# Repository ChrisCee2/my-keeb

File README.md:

# Salsa
Creating a keyboard (Inspired by Littlefoot)<br/>

Images of Type-C pcb:
<br/>

<br/>

<br/>
Guides used:
<br/>
https://wiki.ai03.com/books/pcb-design/page/pcb-guide-part-1---preparations
<br/>
https://www.masterzen.fr/2020/05/03/designing-a-keyboard-part-1/

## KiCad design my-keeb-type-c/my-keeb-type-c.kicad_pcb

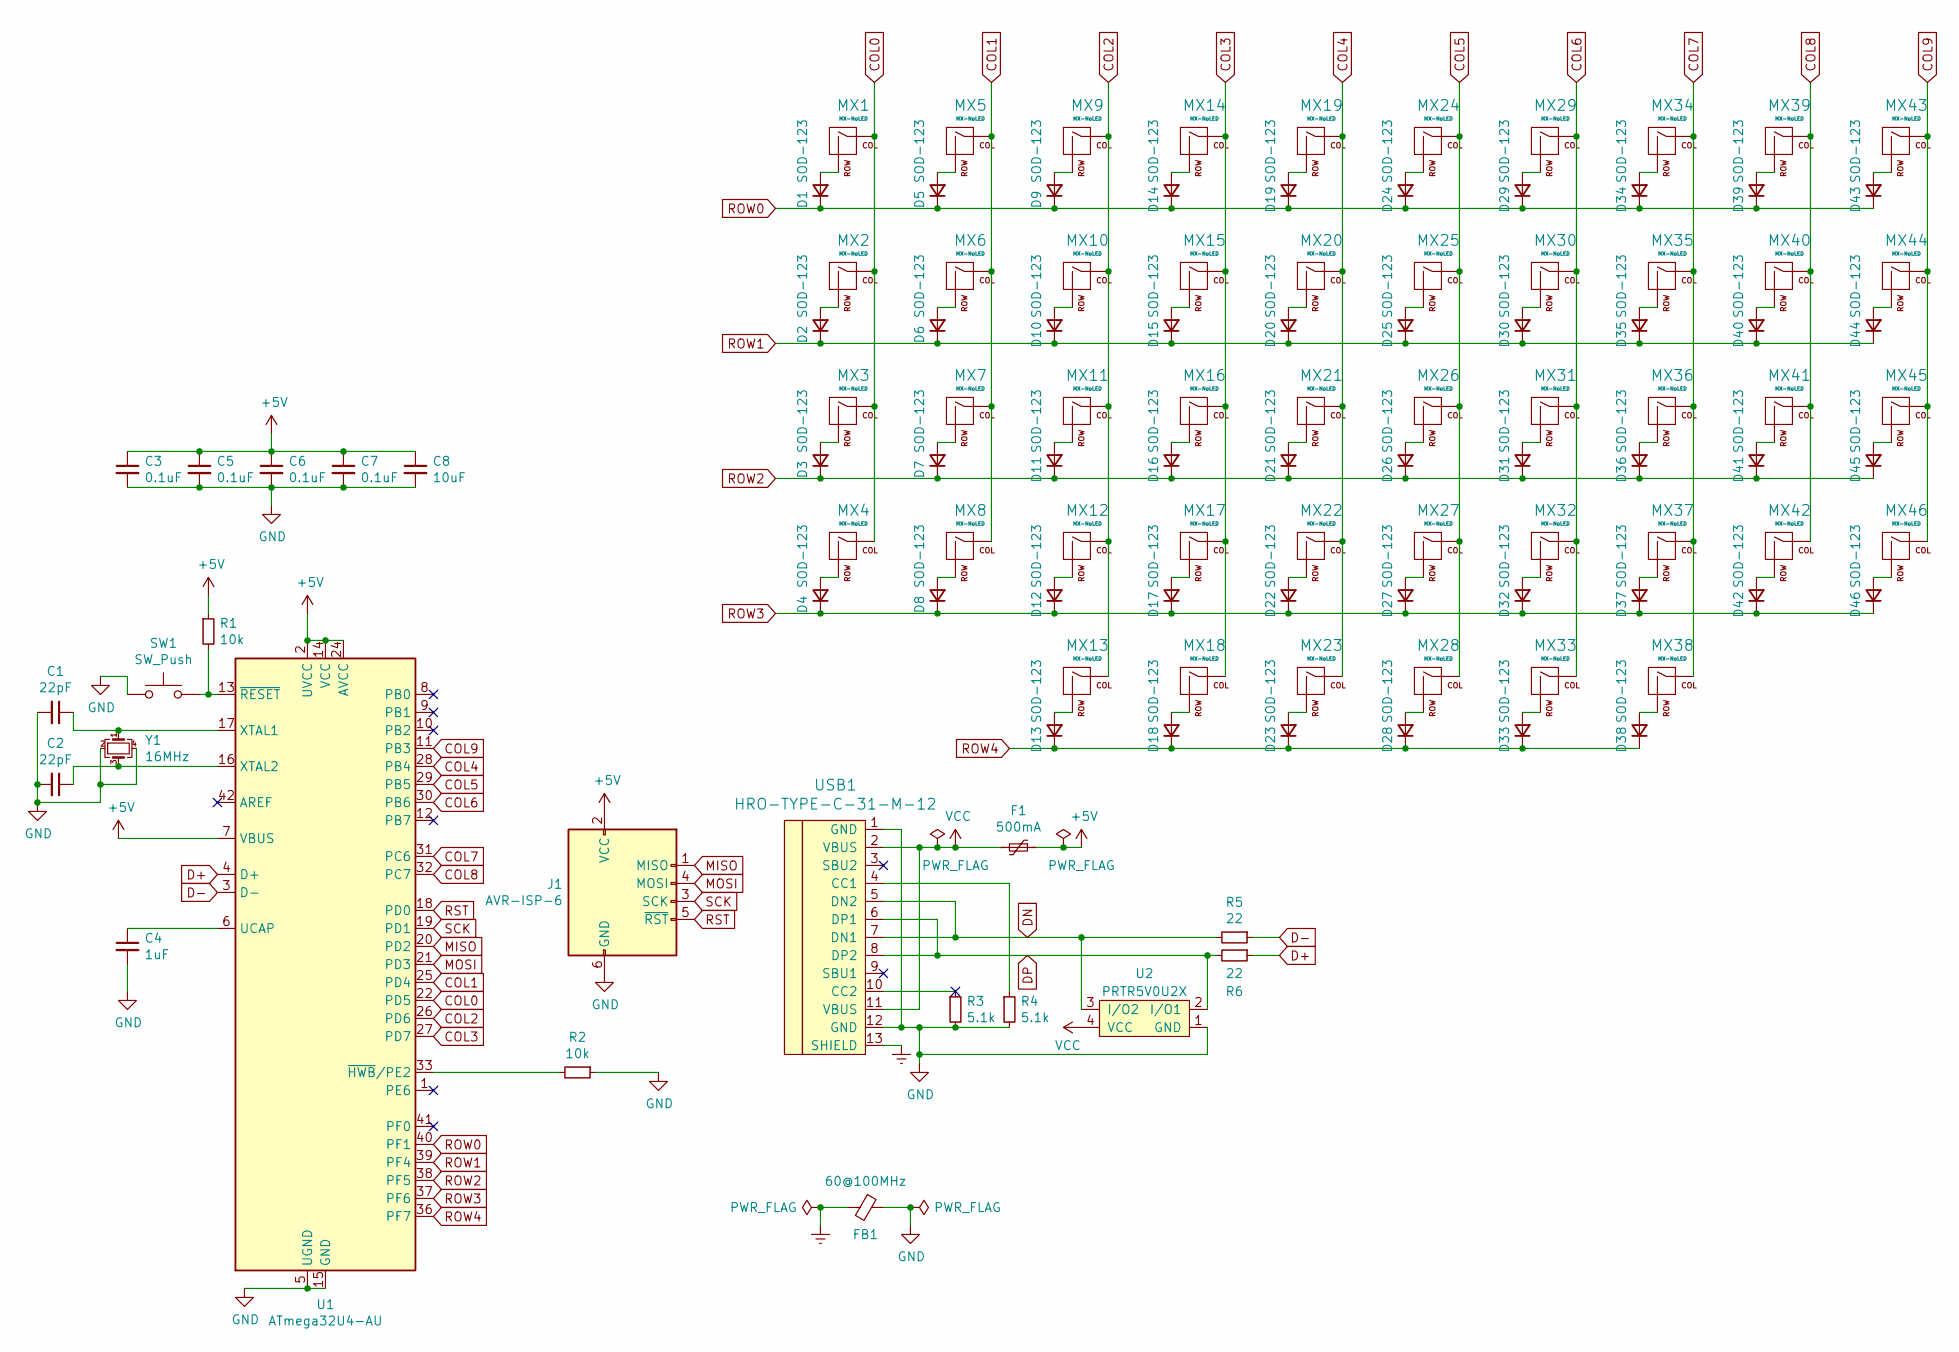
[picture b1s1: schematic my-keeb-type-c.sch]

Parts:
C1, C2: 22pF; C_0805_2012Metric_Pad1.18x1.45mm_HandSolder
C3, C5, C6, C7: 0.1uF; C_0805_2012Metric_Pad1.18x1.45mm_HandSolder
C4: 1uF; C_0805_2012Metric_Pad1.18x1.45mm_HandSolder
C8: 10uF; C_0805_2012Metric_Pad1.18x1.45mm_HandSolder
D1, D2, D3, D4, D5, D6, D7, D8, D9, D10, D11, D12, D13, D14, D15, D16, D17, D18, D19, D20, D21, D22, D23, D24, D25, D26, D27, D28, D29, D30, D31, D32, D33, D34, D35, D36, D37, D38, D39, D40, D41, D42, D43, D44, D45, D46: SOD-123; D_SOD-123
F1: 500mA; Fuse_1206_3216Metric_Pad1.42x1.75mm_HandSolder
FB1: 60@100MHz; L_0805_2012Metric_Pad1.15x1.40mm_HandSolder
J1: AVR-ISP-6; Reset_Pretty-Mask
MX1, MX2, MX3, MX4, MX5, MX6, MX7, MX8, MX9, MX10, MX11, MX12, MX13, MX14, MX15, MX16, MX17, MX18, MX19, MX20, MX21, MX22, MX24, MX25, MX26, MX27, MX29, MX30, MX31, MX32, MX33, MX34, MX35, MX36, MX37, MX38, MX39, MX40, MX41, MX42, MX43, MX44, MX45, MX46: MX-NoLED; MX-1U-NoLED
MX23, MX28: MX-NoLED; MX-1.5U-NoLED
R1, R2: 10k; R_0805_2012Metric_Pad1.20x1.40mm_HandSolder
R3, R4: 5.1k; R_0805_2012Metric_Pad1.20x1.40mm_HandSolder
R5, R6: 22; R_0805_2012Metric_Pad1.20x1.40mm_HandSolder
SW1: SW_Push; SW_SPST_SKQG_WithStem
U1: ATmega32U4-AU; TQFP-44_10x10mm_P0.8mm
U2: PRTR5V0U2X; SOT143B
USB1: HRO-TYPE-C-31-M-12; HRO-TYPE-C-31-M-12-HandSoldering
Y1: 16MHz; Crystal_SMD_3225-4Pin_3.2x2.5mm_HandSoldering

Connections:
+5V: C3.1, C5.1, C6.1, C7.1, C8.1, F1.1, J1.2 (VCC), R1.1, U1.2 (UVCC), U1.7 (VBUS), U1.14 (VCC), U1.24 (AVCC), U1.34 (VCC), U1.44 (AVCC)
COL0: MX1.1 (COL), MX2.1 (COL), MX3.1 (COL), MX4.1 (COL), U1.22 (PD5)
COL1: MX5.1 (COL), MX6.1 (COL), MX7.1 (COL), MX8.1 (COL), U1.25 (PD4)
COL2: MX9.1 (COL), MX10.1 (COL), MX11.1 (COL), MX12.1 (COL), MX13.1 (COL), U1.26 (PD6)
COL3: MX14.1 (COL), MX15.1 (COL), MX16.1 (COL), MX17.1 (COL), MX18.1 (COL), U1.27 (PD7)
COL4: MX19.1 (COL), MX20.1 (COL), MX21.1 (COL), MX22.1 (COL), MX23.1 (COL), U1.28 (PB4)
COL5: MX24.1 (COL), MX25.1 (COL), MX26.1 (COL), MX27.1 (COL), MX28.1 (COL), U1.29 (PB5)
COL6: MX29.1 (COL), MX30.1 (COL), MX31.1 (COL), MX32.1 (COL), MX33.1 (COL), U1.30 (PB6)
COL7: MX34.1 (COL), MX35.1 (COL), MX36.1 (COL), MX37.1 (COL), MX38.1 (COL), U1.31 (PC6)
COL8: MX39.1 (COL), MX40.1 (COL), MX41.1 (COL), MX42.1 (COL), U1.32 (PC7)
COL9: MX43.1 (COL), MX44.1 (COL), MX45.1 (COL), MX46.1 (COL), U1.11 (PB3)
D+: R6.1, U1.4 (D+)
D-: R5.1, U1.3 (D-)
DN: R5.2, U2.3 (I/O2), USB1.5 (DN2), USB1.7 (DN1)
DP: R6.2, U2.2 (I/O1), USB1.6 (DP1), USB1.8 (DP2)
Earth: FB1.2, USB1.13 (SHIELD)
GND: C1.2, C2.2, C3.2, C4.2, C5.2, C6.2, C7.2, C8.2, FB1.1, J1.6 (GND), R2.1, R3.2, R4.2, SW1.1, U1.5 (UGND), U1.15 (GND), U1.23 (GND), U1.35 (GND), U1.43 (GND), U2.1 (GND), USB1.1 (GND), USB1.12 (GND), Y1.2, Y1.4
MISO: J1.1 (MISO), U1.20 (PD2)
MOSI: J1.4 (MOSI), U1.21 (PD3)
unnamed: C1.1, U1.17 (XTAL1), Y1.1
unnamed: C2.1, U1.16 (XTAL2), Y1.3
unnamed: C4.1, U1.6 (UCAP)
unnamed: D1.2 (A), MX1.2 (ROW)
unnamed: D2.2 (A), MX2.2 (ROW)
unnamed: D3.2 (A), MX3.2 (ROW)
unnamed: D4.2 (A), MX4.2 (ROW)
unnamed: D5.2 (A), MX5.2 (ROW)
unnamed: D6.2 (A), MX6.2 (ROW)
unnamed: D7.2 (A), MX7.2 (ROW)
unnamed: D8.2 (A), MX8.2 (ROW)
unnamed: D9.2 (A), MX9.2 (ROW)
unnamed: D10.2 (A), MX10.2 (ROW)
unnamed: D11.2 (A), MX11.2 (ROW)
unnamed: D12.2 (A), MX12.2 (ROW)
unnamed: D13.2 (A), MX13.2 (ROW)
unnamed: D14.2 (A), MX14.2 (ROW)
unnamed: D15.2 (A), MX15.2 (ROW)
unnamed: D16.2 (A), MX16.2 (ROW)
unnamed: D17.2 (A), MX17.2 (ROW)
unnamed: D18.2 (A), MX18.2 (ROW)
unnamed: D19.2 (A), MX19.2 (ROW)
unnamed: D20.2 (A), MX20.2 (ROW)
unnamed: D21.2 (A), MX21.2 (ROW)
unnamed: D22.2 (A), MX22.2 (ROW)
unnamed: D23.2 (A), MX23.2 (ROW)
unnamed: D24.2 (A), MX24.2 (ROW)
unnamed: D25.2 (A), MX25.2 (ROW)
unnamed: D26.2 (A), MX26.2 (ROW)
unnamed: D27.2 (A), MX27.2 (ROW)
unnamed: D28.2 (A), MX28.2 (ROW)
unnamed: D29.2 (A), MX29.2 (ROW)
unnamed: D30.2 (A), MX30.2 (ROW)
unnamed: D31.2 (A), MX31.2 (ROW)
unnamed: D32.2 (A), MX32.2 (ROW)
unnamed: D33.2 (A), MX33.2 (ROW)
unnamed: D34.2 (A), MX34.2 (ROW)
unnamed: D35.2 (A), MX35.2 (ROW)
unnamed: D36.2 (A), MX36.2 (ROW)
unnamed: D37.2 (A), MX37.2 (ROW)
unnamed: D38.2 (A), MX38.2 (ROW)
unnamed: D39.2 (A), MX39.2 (ROW)
unnamed: D40.2 (A), MX40.2 (ROW)
unnamed: D41.2 (A), MX41.2 (ROW)
unnamed: D42.2 (A), MX42.2 (ROW)
unnamed: D43.2 (A), MX43.2 (ROW)
unnamed: D44.2 (A), MX44.2 (ROW)
unnamed: D45.2 (A), MX45.2 (ROW)
unnamed: D46.2 (A), MX46.2 (ROW)
unnamed: R1.2, SW1.2, U1.13 (~RESET)
unnamed: R2.2, U1.33 (~HWB~/PE2)
unnamed: R3.1, USB1.10 (CC2)
unnamed: R4.1, USB1.4 (CC1)
ROW0: D1.1 (K), D5.1 (K), D9.1 (K), D14.1 (K), D19.1 (K), D24.1 (K), D29.1 (K), D34.1 (K), D39.1 (K), D43.1 (K), U1.40 (PF1)
ROW1: D2.1 (K), D6.1 (K), D10.1 (K), D15.1 (K), D20.1 (K), D25.1 (K), D30.1 (K), D35.1 (K), D40.1 (K), D44.1 (K), U1.39 (PF4)
ROW2: D3.1 (K), D7.1 (K), D11.1 (K), D16.1 (K), D21.1 (K), D26.1 (K), D31.1 (K), D36.1 (K), D41.1 (K), D45.1 (K), U1.38 (PF5)
ROW3: D4.1 (K), D8.1 (K), D12.1 (K), D17.1 (K), D22.1 (K), D27.1 (K), D32.1 (K), D37.1 (K), D42.1 (K), D46.1 (K), U1.37 (PF6)
ROW4: D13.1 (K), D18.1 (K), D23.1 (K), D28.1 (K), D33.1 (K), D38.1 (K), U1.36 (PF7)
RST: J1.5 (~RST), U1.18 (PD0)
SCK: J1.3 (SCK), U1.19 (PD1)
VCC: F1.2, U2.4 (VCC), USB1.2 (VBUS), USB1.11 (VBUS)

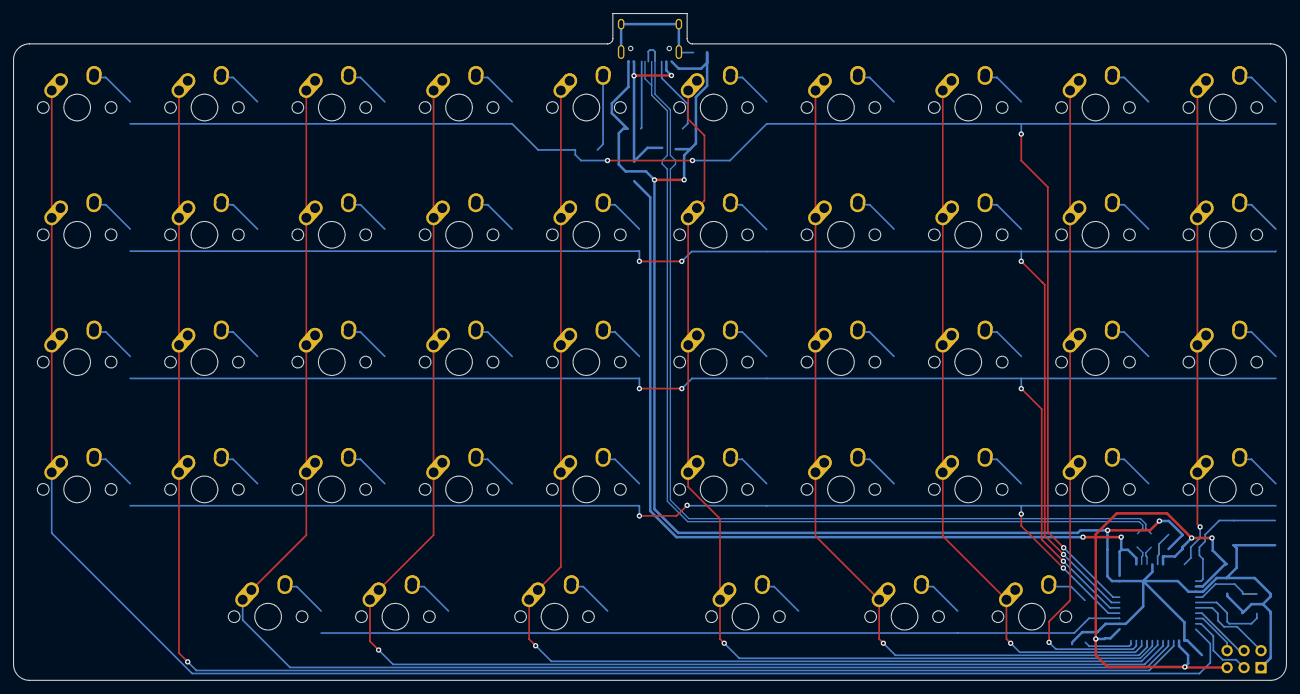
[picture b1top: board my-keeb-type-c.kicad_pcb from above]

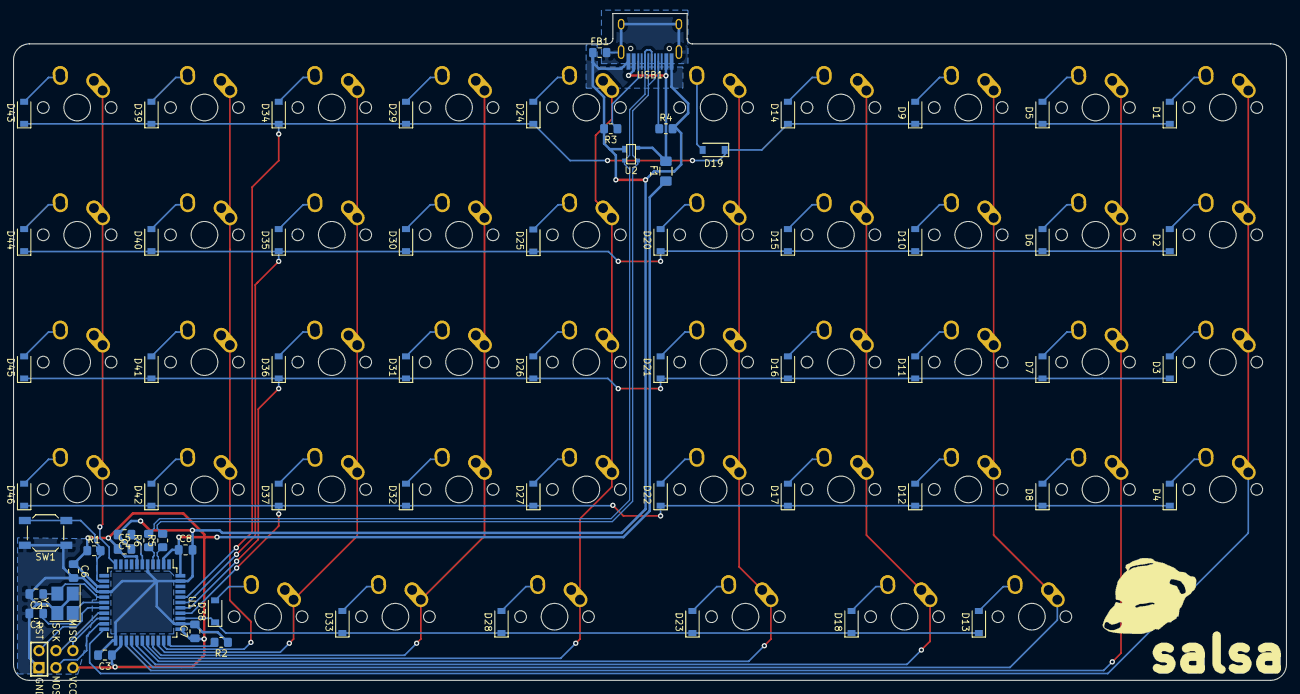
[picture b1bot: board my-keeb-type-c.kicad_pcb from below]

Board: 2 copper layers, 190.5 x 99.8 mm, 114 parts (68 on the bottom side), 80 nets.

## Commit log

2021-12-24 Create kicad project and added submodules
2021-12-24 Deleted directory
2021-12-24 Added libraries
2021-12-25 Worked on schema
2021-12-27 Finished schema
2021-12-28 Worked on PCB
2021-12-28 Routing in progress
2021-12-28 Still working on routing
2021-12-28 Still doing routing
2021-12-29 Working on matrix
2021-12-30 Finished routing
2021-12-30 Finished designing the pcb!
2021-12-30 Generated gerber files
2021-12-30 Added gerber zip
2021-12-31 Creating pro micro pcb
2021-12-31 Added pro micro library
2021-12-31 Updated my-keeb pcb
2021-12-31 Added pro micro to pcb, routing WIP
2021-12-31 Added some footprints prettys
2021-12-31 Promicro pcb uses hybrid diodes
2021-12-31 Finished pro micro pcb
2022-01-01 Working on making it two parts
2022-01-01 Working on part2 pcb
2022-01-01 Fixed track issues
2022-01-01 part2 wip routing
2022-01-02 Finished modular pcb
2022-01-02 Added type c usb lib
2022-01-03 Finished type c model
2022-01-03 Improved USB routing for original my-keeb
2022-01-03 Added images
2022-01-03 Organized files
2022-01-03 Updated submodule paths
2022-01-03 Reverted
2022-01-03 Fixed some stuff
2022-01-03 Finished type c modular pcb part 1
2022-01-04 Finished type c part 2 and updated type c part 1
2022-01-04 Made sasha smaller
2022-01-07 Created some plateless gasket mount pcbs
2022-01-20 Added a gasket mount case file
2022-01-21 Deleted overhang on port for bottom case
2022-01-23 Added layout files
2022-01-23 Added test stuff, stuff im workign on
2022-02-10 Added new case that hides nuts
2022-02-26 Added octopus case
2022-02-26 Added more fillet to octopus case
2022-03-14 Case with thicker bezels
2022-03-27 Organized files to different folders
2022-03-27 Moved my-keeb to pcb folder
2022-09-09 Added logo to pro micro model
2022-09-13 Added gasket mount to pro micro pcb
